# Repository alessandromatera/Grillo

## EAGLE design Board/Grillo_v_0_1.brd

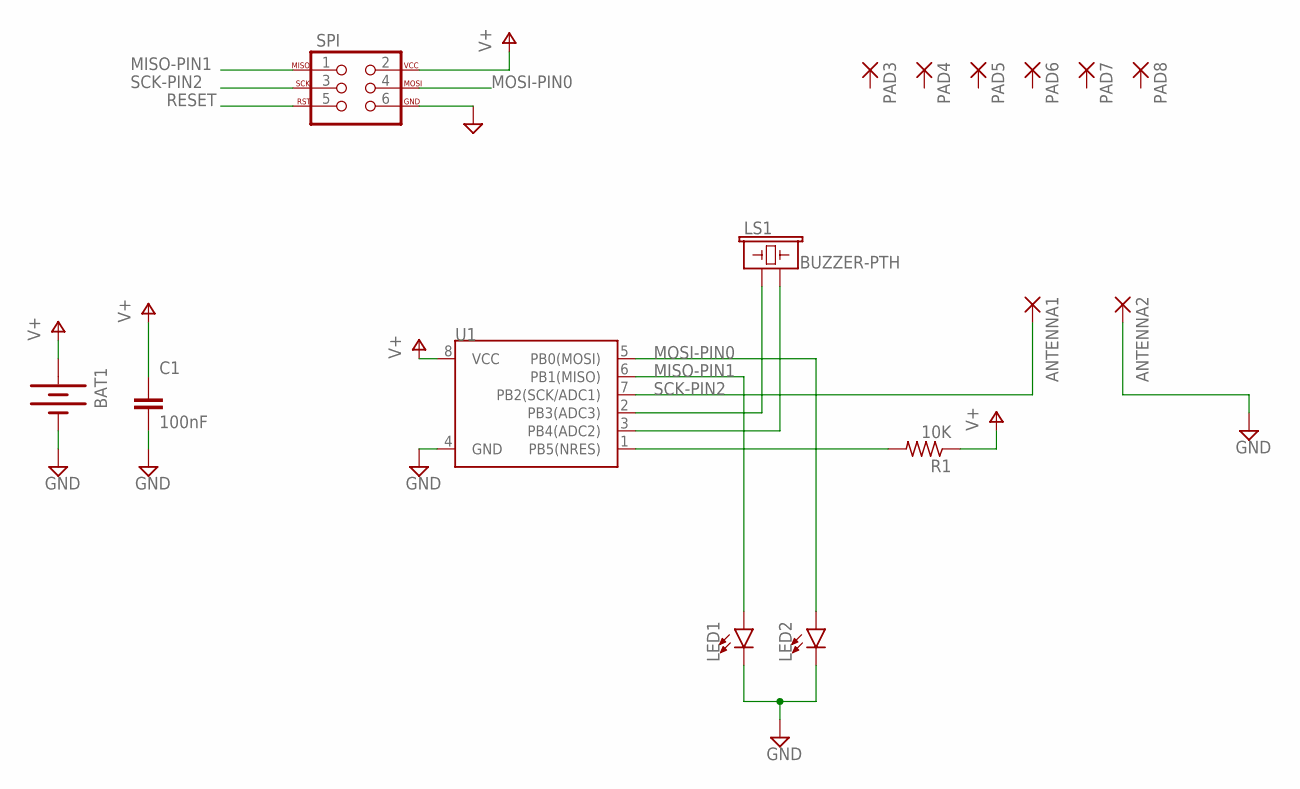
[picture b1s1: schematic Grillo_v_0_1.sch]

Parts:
ANTENNA1, ANTENNA2: 1,6/0,9
BAT1: BATTERY20PTH; BATTCOM_20MM_PTH
C1: 100nF; C050-024X044
LED1, LED2: LED3MM; LED_3MM
LS1: BUZZER-PTH; BUZZER-12MM
PAD3, PAD4, PAD5, PAD6, PAD7, PAD8: 1,6/0,9
R1: 10K; 0204/7
SPI: AVR_SPI_PROG_3X2PTH; 2X3
U1: ATTINY45TINY85-20-DIP; DIP08

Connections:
GND: ANTENNA2.1, BAT1.2 (-), C1.2, LED1.K (C), LED2.K (C), SPI.6, U1.4 (GND)
MISO-PIN1: LED1.A, SPI.1, U1.6 (PB1(MISO))
MOSI-PIN0: LED2.A, SPI.4, U1.5 (PB0(MOSI))
unnamed: LS1.+ (1), U1.2 (PB3(ADC3))
unnamed: LS1.- (2), U1.3 (PB4(ADC2))
RESET: R1.2, SPI.5, U1.1 (PB5(NRES))
SCK-PIN2: ANTENNA1.1, SPI.3, U1.7 (PB2(SCK/ADC1))
V+: BAT1.1 (+), C1.1, R1.1, SPI.2, U1.8 (VCC)

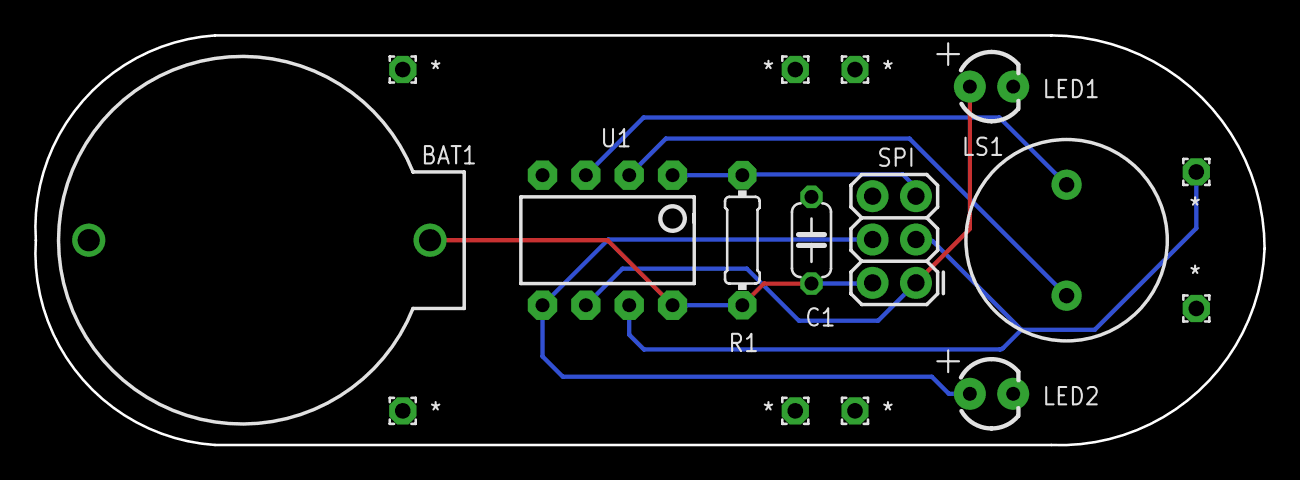
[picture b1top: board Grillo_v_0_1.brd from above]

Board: 2 copper layers, 72.0 x 24.0 mm, 16 parts (0 on the bottom side), 8 nets.

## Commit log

2019-10-26 Grillo V1

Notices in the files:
parts and their libraries:
SparkFun-DigitalIC: Licensing: CC v3.0 Share-Alike You are welcome to use this library for commercial purposes.
SparkFun-LED: Licensing: Creative Commons ShareAlike 4.0 International - https://creativecommons.org/licenses/by-sa/4.0
